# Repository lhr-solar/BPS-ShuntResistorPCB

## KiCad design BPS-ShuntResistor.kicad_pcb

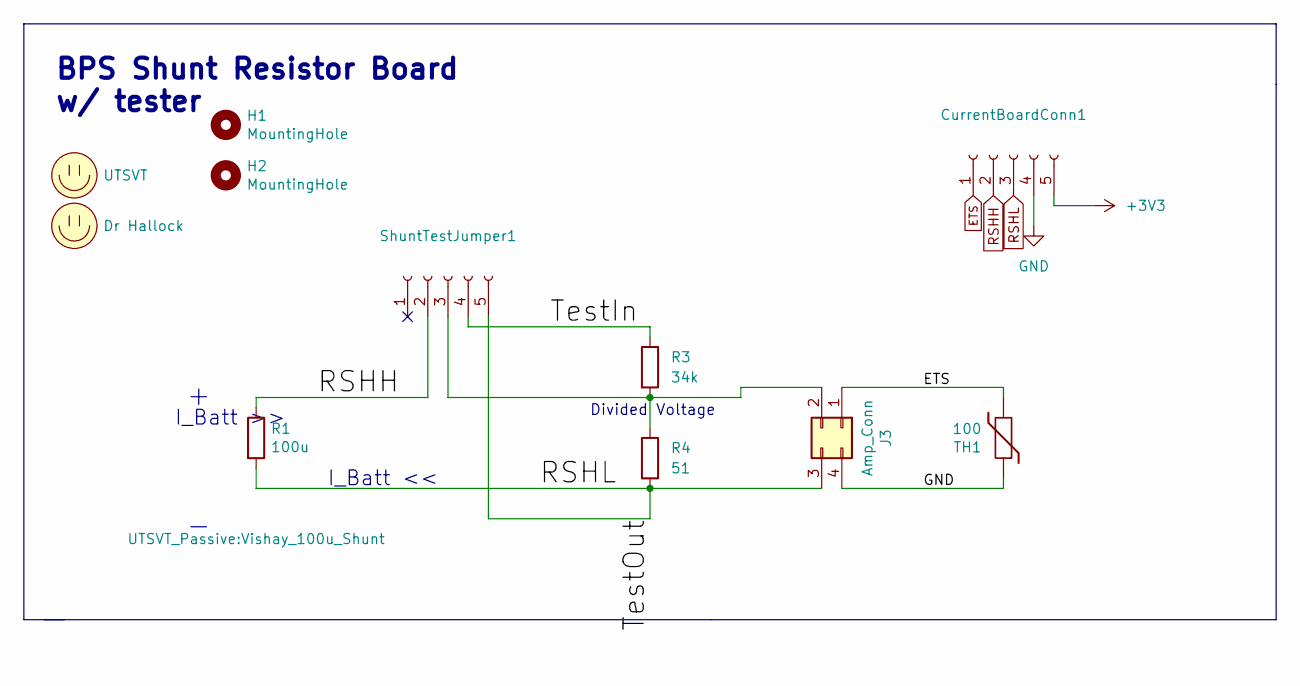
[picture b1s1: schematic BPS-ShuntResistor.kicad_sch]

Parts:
CurrentBoardConn1: (no value)
H1, H2: MountingHole; MountingHole_2.7mm_M2.5
J3: Amp_Conn; Power_Metal_Strip_Battery_Shunt_Resistor_4_Pin_Connector
LOGO1: UTSVT; UTSVT_Logo_Symbol
LOGO2: Dr Hallock; Hallock_Image_Tiny
R1: 100u; Vishay_100u_Shunt
R3: 34k; R_0805_2012Metric
R4: 51; R_0805_2012Metric
ShuntTestJumper1: (no value)
TH1: 100; R_0805_2012Metric

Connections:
+3V3: CurrentBoardConn1.5
/TestIn: R3.1, ShuntTestJumper1.4
ETS: CurrentBoardConn1.1, J3.1, TH1.2
GND: CurrentBoardConn1.4, J3.4, TH1.1
unnamed: J3.2, R3.2, R4.1, ShuntTestJumper1.3
RSHH: CurrentBoardConn1.2, R1.1, ShuntTestJumper1.2
RSHL: CurrentBoardConn1.3, J3.3, R1.2, R4.2, ShuntTestJumper1.5

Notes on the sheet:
I_Batt <<
Divided Voltage
+ -
BPS Shunt Resistor Board w/ tester
I_Batt >>

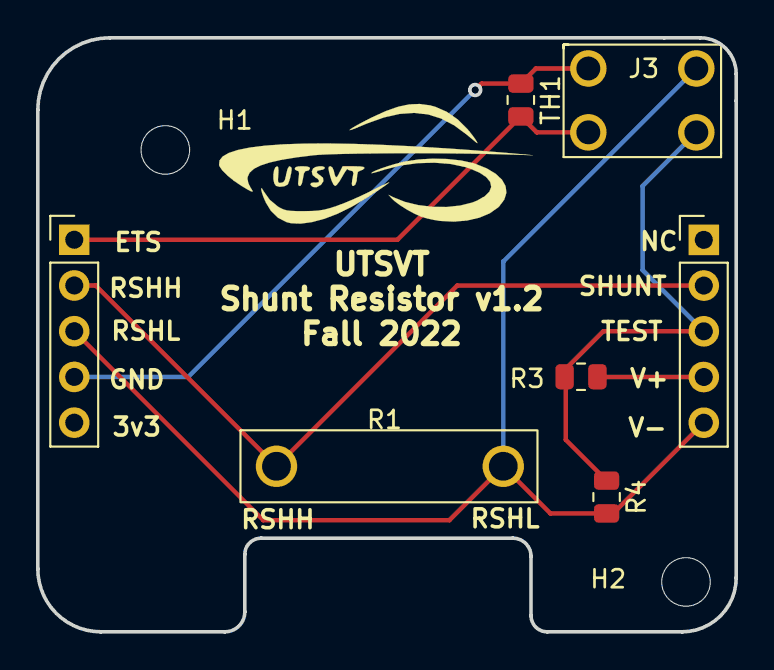
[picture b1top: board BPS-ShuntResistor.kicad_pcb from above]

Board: 2 copper layers, 38.8 x 33.0 mm, 11 parts (1 on the bottom side), 6 nets.

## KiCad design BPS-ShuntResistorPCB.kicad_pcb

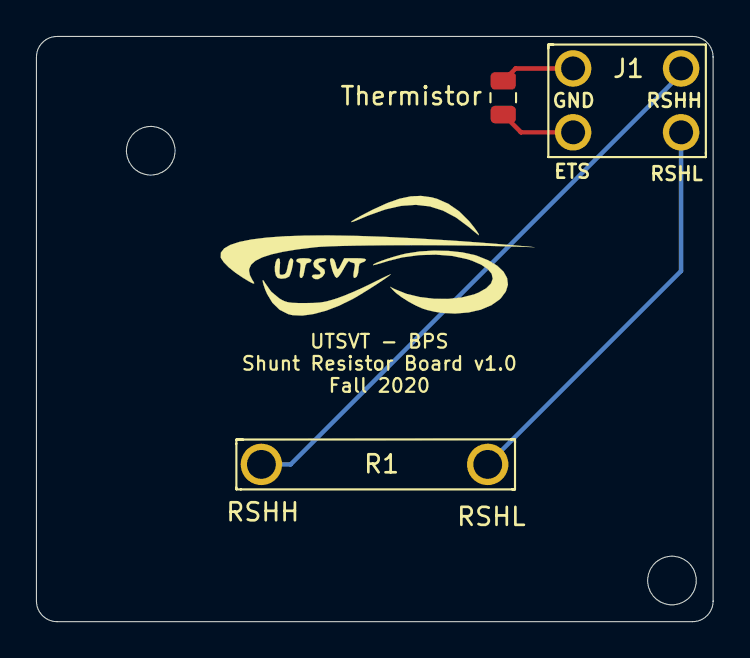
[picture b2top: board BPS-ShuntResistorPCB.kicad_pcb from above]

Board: 2 copper layers, 37.6 x 32.5 mm, 7 parts (1 on the bottom side), 4 nets.

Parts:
H1, H2: MountingHole; MountingHole_2.7mm_M2.5
J1: Amp_Conn; Power_Metal_Strip_Battery_Shunt_Resistor_4_Pin_Connector
LOGO1: UTSVT; UTSVT_Logo_Symbol
LOGO2: Dr Hallock; Hallock_Image_Tiny
R1: 100u; Power_Metal_Strip_Battery_Shunt_Resistor
Thermistor: 100; R_0805_2012Metric

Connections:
/ETS: J1.1, Thermistor.2
/GND: J1.4, Thermistor.1
/RSHH: J1.3, R1.1
/RSHL: J1.2, R1.2

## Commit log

2020-09-05 test that branch is working
2020-09-05 inital schematic
2020-09-05 Adds submodule to the repo
2020-09-05 fixed labels
2020-09-05 added logos and conn footprint
2020-09-07 updated connector to match ampere board
2020-09-12 added resistor footprint
2020-09-26 needs to be reviewed
2020-09-26 implemented edits
2020-09-26 fixed typo
2020-09-26 more edits
2020-09-26 Creates gerbers
2020-09-26 Creates gerber edits to the PCB
2020-10-03 Adds QuAC
2020-10-03 Initial board dev (#2)
    * added logos and conn footprint
    * updated connector to match ampere board
    * added resistor footprint
    * needs to be reviewed
    * implemented edits
    * fixed typo
2020-10-03 Removes Gerbers since added to release
2020-10-17 Organizes schematic and creates pdf and png files of schematic and PCB
2020-10-17 Changes to naming convention w/out PCB suffix
2022-09-17 banana connectors for rshh and rshl
    10mm track width on top to handle up to 130A current, bottom of board is normal connectors from the 4 pin connector
2022-09-17 Fixing libraries
2022-09-17 working on voltage divider - better resolution; need to make footprint for the shunt resistor proper
2022-09-18 working on new footprint for shunt resistor
2022-09-18 trying to figure out the schematic
2022-09-19 Adding voltage divider for tests
    Net labels to allow voltage divider/shunt resistor to all work properly.
    Voltage divider stays separate from the shunt itself, but divides down to the shunt resistor voltage levels, such that we can route the voltage divider values directly into the current monitor.
2022-09-24 working on new board
    connector for current board, testing for shunt
2022-09-24 Update UTSVT-KiCadLibraries
2022-09-24 pcb v1 not done
2022-09-24 added more info per manthan
    might need more changes
2022-10-01 Adjusting shunt-current connector pins
    Tianda and I haven't really decided on footprint stuff yet but pins now line up.
2022-10-01 Update gitignore to allow BOM file
2022-10-01 Updated BOM csv with approximate prices and potential Mouser lists
    Ignore PCB update, footprint for 1x5 connector not decided
2022-10-08 Mouser-generated BOM and parts list
    See the .XLS file for info
2022-10-15 Working on new layout
    Kind of messy
2022-10-15 switch footprint is invalid agony
2022-10-15 working on it
2022-10-22 version 1 of the pcb redesign
2022-10-22 still working on layout.
    i want to double check some footprints.
2022-10-22 updating custom board parts
2022-10-22 added new switch, updated board and schematic
2022-10-22 sch didn't save
2022-10-26 reworking w tianda on sat
2022-10-29 reorganizing board
    workign on sync between amp board and this one
2022-11-01 working on rework
2022-11-01 fixing sch
2022-11-05 aligning with current board
2022-11-05 nothing actually changed
    kicad funny floating point things
2022-11-05 Fixed RSHL/RSHH connectors
    Net labels were in wrong spot on circuit
2022-11-05 moved to exact same positions as tianda
2022-11-09 rounding corners, making board a bit smaller
2022-11-12 fixing pcb to look nicer
2022-11-12 resistor placement change
    make tracks more readable + add some text for pins
2022-11-12 added gerber and drill files
    per JLC's requirements
2022-11-16 Fixed silkscreens
2022-11-17 generated gerber and drill files
    again
2022-11-21 finishing touches
    adjusted logo positions, added creation information text, regenerated drill and gerber files just in case.
2023-01-14 fixes so the holes are big enough
    shunt resistor pads were too small increased to 2.2mm
2023-01-21 update board and create gerber/drills
    BOM on my mouser account (only 34k and 51 ohm resistors)
2023-01-21 update bom
2023-01-21 Update shunt holes to be old board size
    and gerbers made
2023-01-21 fix resistor bom to be 0805
    mouser cart fixed too
2023-01-21 regen gerbers and drills
2023-02-04 shunt board zip gerbers
